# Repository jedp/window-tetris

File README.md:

# Window Tetris

Arduino-based Tetris game to render using a large grid of 5050 RGB LEDs,
controlled by means of a Covid-friendly foot controller.

The goal is to mount the display outside, facing the street, so that passers-by
can play using the foot controller on the sidewalk.

## Current Status

Done: game engine that plays and scores according to the classic rules.

In progress:

- The LED mounts have become a little project on their own.
  See [jedp/RGB5050-mount](https://github.com/jedp/RGB5050-mount) for a
  small and versatile PCB mount.

TBD:

- Build and be driven by external foot controller (parts ordered)

## Unit Tests

On native: `pio test -e native`

On attached Arduino device: `pio test -e uno`

The native tests are run automatically by travis. But please be sure to test
on a device before submitting changes.

## License

Written by Jed Parsons. Distributed under the BSD license. Read `license.txt`
for details. All text above must be included in any redistribution.

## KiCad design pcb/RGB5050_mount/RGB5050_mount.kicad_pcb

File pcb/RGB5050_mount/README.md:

This directoy contains KiCad files for chainable mounts for the RGB LEDs.

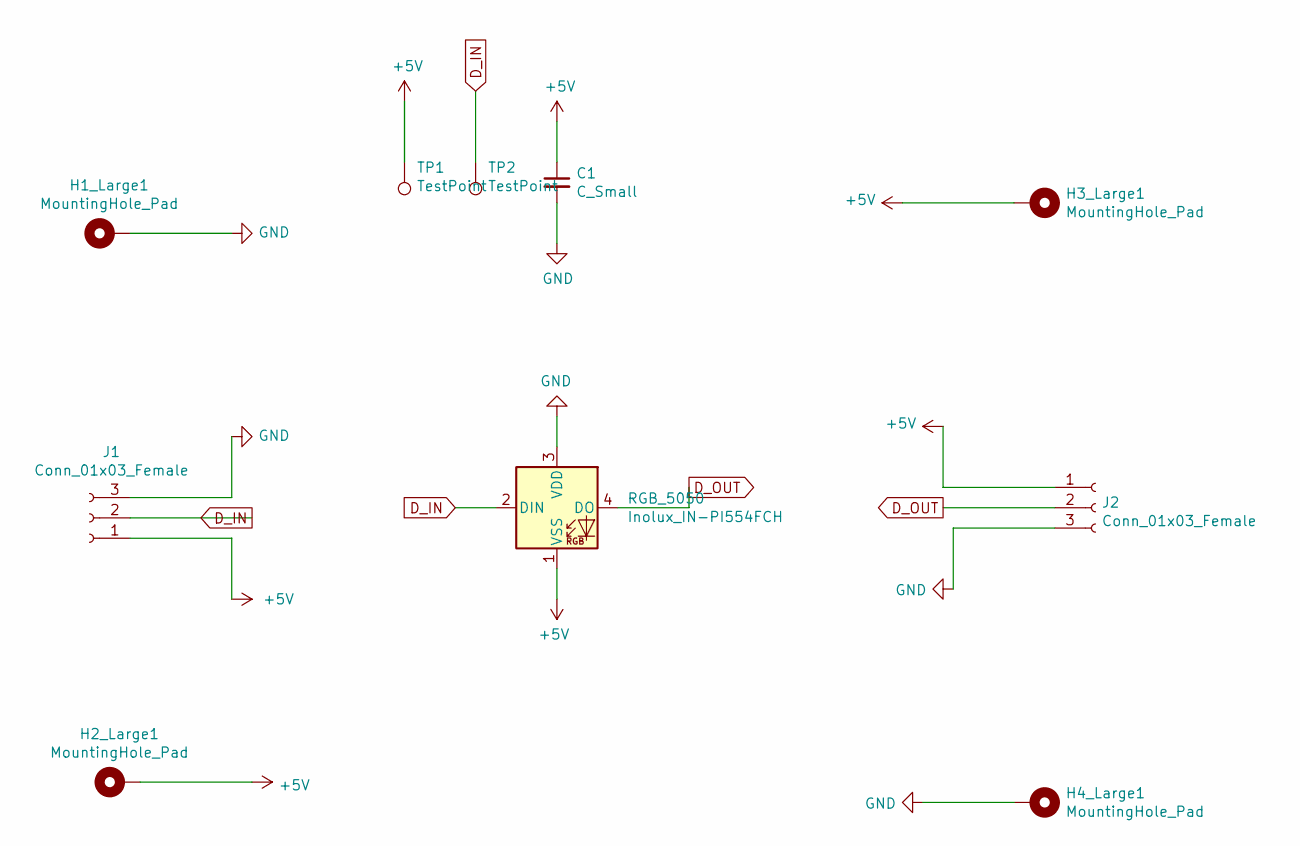
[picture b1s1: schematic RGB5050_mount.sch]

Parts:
C1: C_Small; C_0805_2012Metric
H1_Large1, H2_Large1, H3_Large1, H4_Large1: MountingHole_Pad; MountingHole_2.5mm_Pad
J1, J2: Conn_01x03_Female; PinHeader_1x03_P2.54mm_Vertical
RGB_5050: Inolux_IN-PI554FCH; LED_Inolux_IN-PI554FCH_PLCC4_5.0x5.0mm_P3.2mm
TP1, TP2: TestPoint; TestPoint_THTPad_D1.0mm_Drill0.5mm

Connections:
+5V: C1.1, H2_Large1.1, H3_Large1.1, J1.1, J2.1, RGB_5050.1 (VSS), TP1.1
D_IN: J1.2, RGB_5050.2 (DIN), TP2.1
D_OUT: J2.2, RGB_5050.4 (DO)
GND: C1.2, H1_Large1.1, H4_Large1.1, J1.3, J2.3, RGB_5050.3 (VDD)

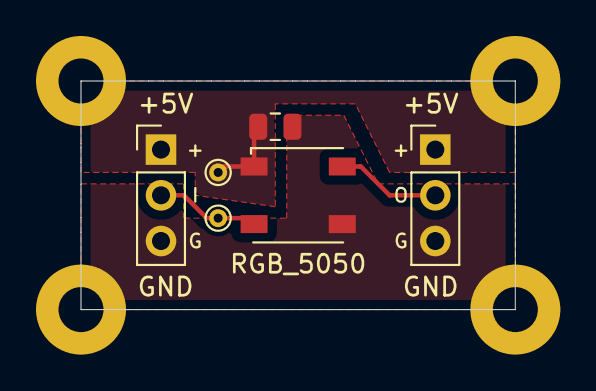
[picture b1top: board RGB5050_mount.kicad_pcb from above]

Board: 2 copper layers, 24.1 x 12.7 mm, 10 parts (0 on the bottom side), 4 nets.

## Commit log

2020-06-18 Window-box tetris. Initial commit of some geometry.
2020-06-18 Struct to contain pieces, their orientation, and bounding boxes
2020-06-18 Valid placement withing bounds
2020-06-18 Move shape_t to geom.h, and make the board a shape_t
2020-06-18 Collision test for piece on board
2020-06-18 Make shape grid mutable; Stick shape to grid
2020-06-18 Rename validPlacement to inBounds
2020-06-19 Fix nits; make it compile with platformio
    pio run -e uno
    pio test
2020-06-19 Convert row,col int pairs to a point_t
    Fixed some small nits.
    Not sure how to prevent main.cc from being run in unit tests.
    Can't get src_filter to work. Excluding with #ifndef UNIT_TEST for now.
2020-06-19 Comments
2020-06-19 Generator for sequence of pieces
    Test needs to be moved to use Arduino.h so we can test with
    random().
2020-06-19 Random number generator
    Adds unit tests for attached Arduino
    Local (native) tests use mock RNG. Arduino tests use Arduino
    random() method with fixed seed.
2020-06-19 Add travis ci for native unit tests
2020-06-20 Initial game class structure; some improvements
2020-06-20 Remove bad import (no iostream for arduino!)
2020-06-20 Introduce produceNextPiece method
2020-06-20 Remove rows,cols from piece_t; Add currentShape
2020-06-20 Convert piece from struct to class
2020-06-20 Convert shape from struct to class
2020-06-20 Convert stick() function to drop() methond on Shape
2020-06-20 Refactor collide to method on Shape
2020-06-20 Generate first shape; Render board and piece on canvas
2020-06-21 Move pieces left and right
2020-06-21 Piece sticks at bottom; Rotate pieces
2020-06-21 Drop piece all the way
2020-06-21 Add game-over callback
2020-06-22 Callback on game over
2020-06-22 Scoring for dropping pieces; Reset rotation when piece appears
2020-06-22 Mark and clear full rows.
    After dropping or time advancing (tick()), we check for full rows.
    Full rows are all converted to the 'X' character and rendered for a
    tick. The display manager can do something interesting with this.
    On the subsequent tick, the rows are removed from the board, everything
    slides down accordingly, and the score is updated.
2020-06-22 Fix reorder errors in game.h, game.cc
2020-06-22 Documentation and clean-up
2020-06-22 Add -Wstrict-prototypes -Wshadow
2020-06-22 Remove spurious tests and dead code; cpplint all the things.
2020-06-22 Updated README notes
2020-06-23 add CPPLINT.cfg
2020-07-02 More C; Less Java
    The implementation so far (b0e50c6) works well, but it's looking
    like Enterprise Tetris. Layers of abstraction, dependency injection,
    etc., beyond what we need for a tiny embedded project.
    This is a second attempt, written in hopefully leaner C.
    C++ version with main.cc instantiating a Game():
    RAM: [======= ] 66.7% (used 1367 bytes from 2048 bytes)
2020-07-02 Echo grid over serial for debugging; Script to draw with curses
2020-07-03 Hack for debugging; Play game using Serial.println as display
2020-07-06 Pixel test
    Cycle some pixels through the range of hues.
2020-10-07 PCB for mounting the RGB 5050s
2020-10-08 Updates; link to jedp/RGB5050-mount
